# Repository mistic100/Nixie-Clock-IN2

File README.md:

# Nixie Clock IN-2

Check out my other projects:
- [Nixie Clock IN14](https://github.com/mistic100/Nixie-Clock-IN14)
- [Nixie Clock IN12](https://github.com/mistic100/Nixie-Clock-IN12)
- [IV-27 VFD Clock](https://github.com/mistic100/IV-27-Clock)

This is a Nixie Clock using small [IN-2 tubes](https://www.tube-tester.com/sites/nixie/data/I/IN-2/in-2.htm) and a 16x9 LED matrix. It was mostly inspired by this 3D model [80s Alarm Clock by Tom Seddon](https://sketchfab.com/3d-models/80s-alarm-clock-36aaecc458bc4e3ea907cdb9d538c9f1).

[More photos](https://photos.strangeplanet.fr/index.php?/category/268-horloge_nixie_in_2_mars_2026)

### Key features

- 3 buttons and 1 rotary encoder
- Zigbee connectivity
  - receive date-time
  - receive weather
  - send room temperature and humidity
  - can be toggled on/off
  - 3 generic buttons send click, double click, long click events
- small LED matrix with multiple screens
  - scrolling date
  - temperature
  - falling sand animation
  - Game of Life animation
  - fire animation
  - rain animation
- possibility to use a DS3231 RTC module (routed on the PCB but not available in current firmware)

### BOM

- ESP32-C6 SuperMini
- Adafruit Charlieplexed 16x9 LED matrix + IS31FL3731 driver
- 4x IN-2 Nixie tubes
- 2x INS-1 Nixie indicators
- Microchip HV5222 serial-to-parallel converter
- Adafruit 4 channels TTL level-shifter
- 4x APA106 5mm adressable LEDs
- BME280 ambient sensor
- EC11 rotary encoder
- 3x 6x6x4.3mm push buttons
- MPSA42 high voltage NPN transistor
- USB-C connector
- resistors, capacitors, diodes...

### Schematics

### PCB

### Case

## License

The Arduino code, the KiCad design and SolidWorks files are distributed under the Creative Commons 3.0 BY-SA license.

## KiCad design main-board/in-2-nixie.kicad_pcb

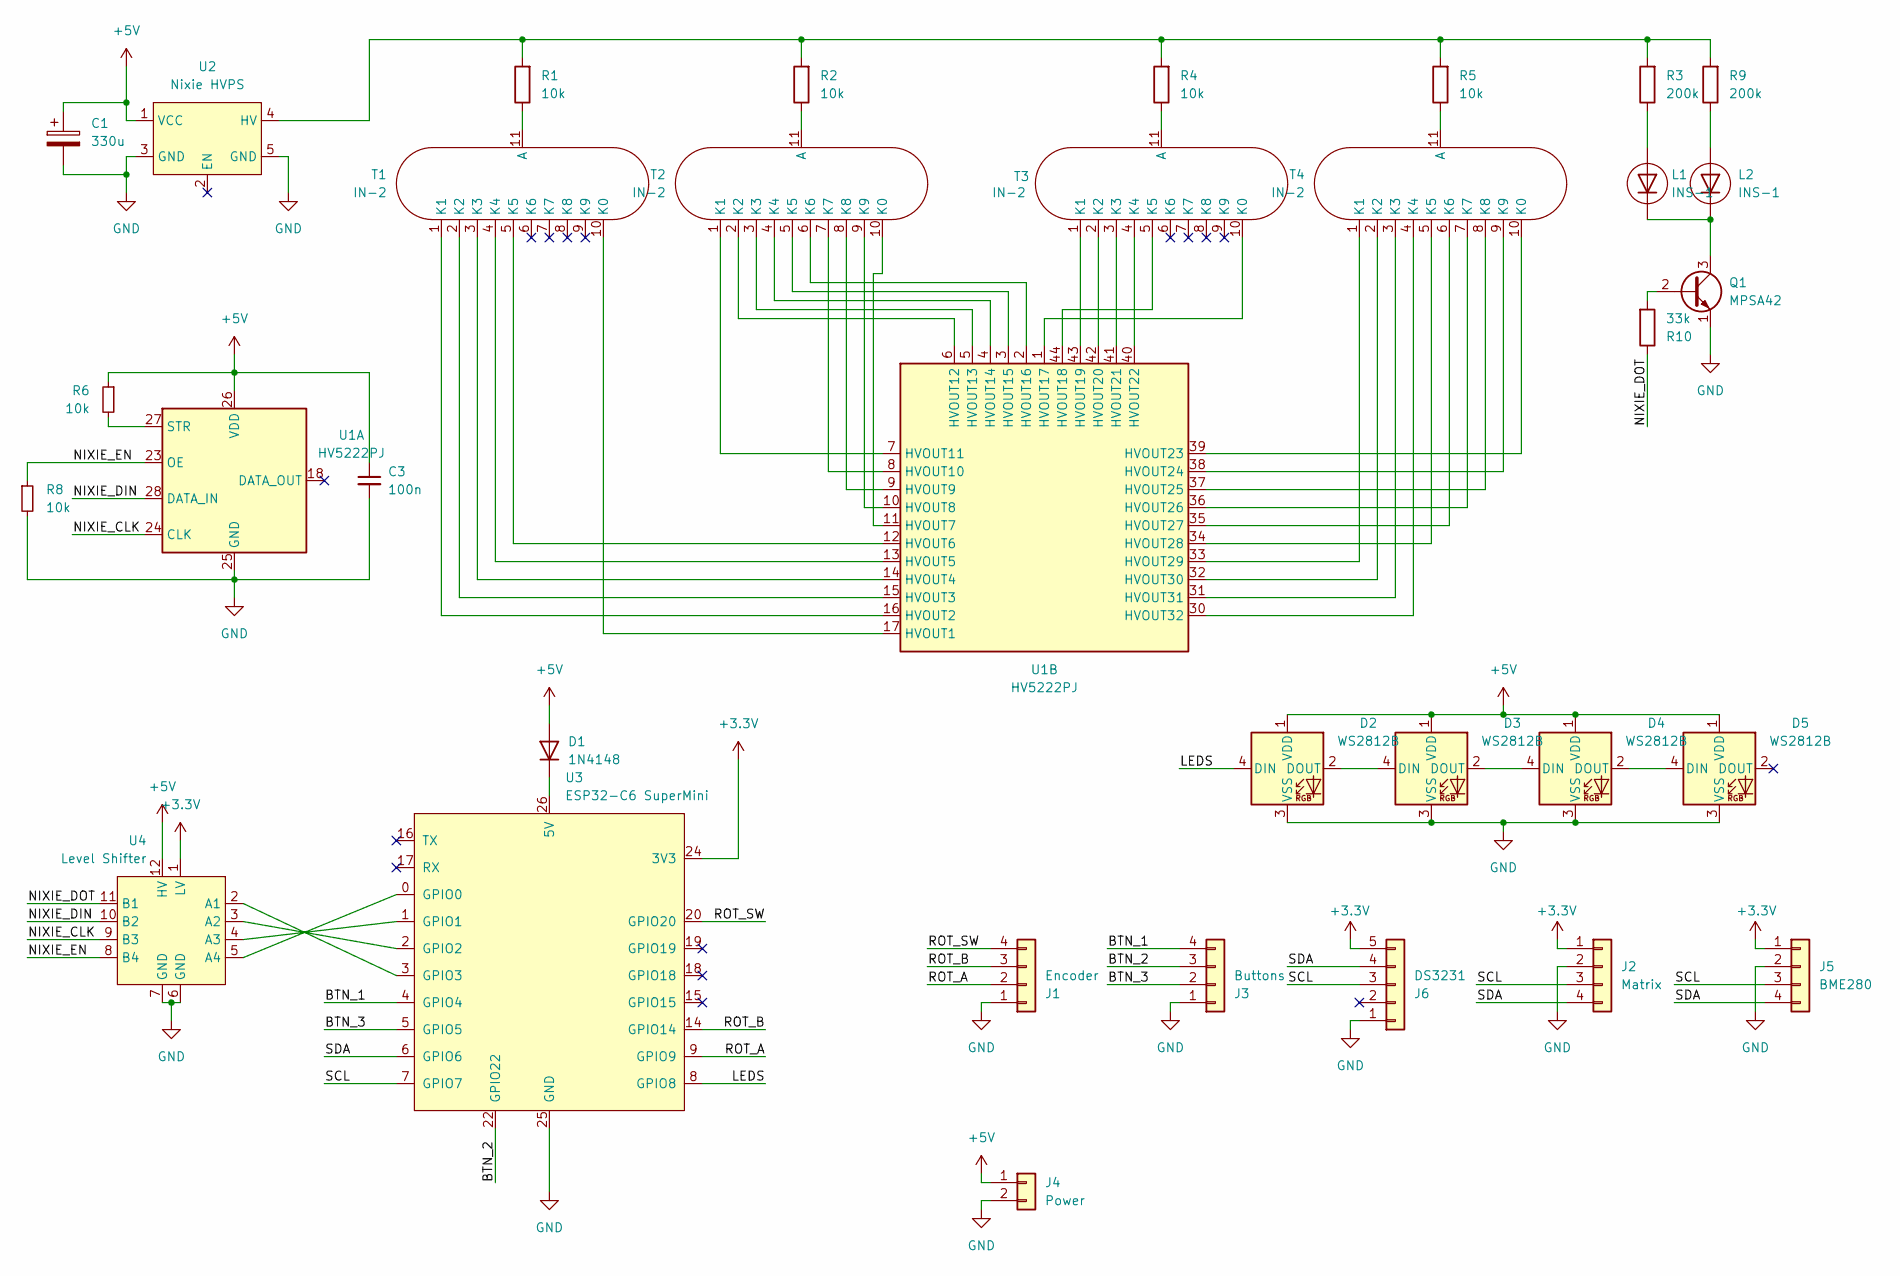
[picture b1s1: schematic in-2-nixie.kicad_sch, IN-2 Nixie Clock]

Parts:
C1: 330u; CP_Radial_D8.0mm_P3.50mm
C3: 100n; C_Disc_D5.0mm_W2.5mm_P5.00mm
D1: 1N4148; D_DO-35_SOD27_P7.62mm_Horizontal
D2, D3, D4, D5: WS2812B; APA106_D5-Staggered_Pins
J1: Encoder; PinHeader_1x04_P2.54mm_Vertical
J2: Matrix; PinHeader_1x04_P2.54mm_Vertical
J3: Buttons; PinHeader_1x04_P2.54mm_Vertical
J4: Power; JST_XH_B2B-XH-A_1x02_P2.50mm_Vertical
J5: BME280; PinHeader_1x04_P2.54mm_Vertical
J6: DS3231; PinHeader_1x05_P2.54mm_Vertical
L1, L2: INS-1; INS-1 Nixie Tube
Q1: MPSA42; TO-92_Inline
R1, R2, R4, R5: 10k; R_Axial_DIN0207_L6.3mm_D2.5mm_P7.62mm_Horizontal
R3, R9: 200k; R_Axial_DIN0207_L6.3mm_D2.5mm_P7.62mm_Horizontal
R6, R8: 10k; R_Axial_DIN0207_L6.3mm_D2.5mm_P2.54mm_Vertical
R10: 33k; R_Axial_DIN0207_L6.3mm_D2.5mm_P2.54mm_Vertical
T1, T2, T3, T4: IN-2; IN-2 Nixie Tube (w. pins)
U1: HV5222PJ; PLCC-44 LongPads
U2: Nixie HVPS; Neonwork Nixie Power Supply
U3: ESP32-C6 SuperMini
U4: Level Shifter; Adafruit Level Shifter

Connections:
+3.3V: J2.1, J5.1, J6.5, U3.24 (3V3), U4.1 (LV)
+5V: C1.1, C3.1, D1.2 (A), D2.1 (VDD), D3.1 (VDD), D4.1 (VDD), D5.1 (VDD), J4.1, R6.1, U1.26 (VDD), U2.1 (VCC), U4.12 (HV)
/BTN_1: J3.4, U3.4 (GPIO4)
/BTN_2: J3.3, U3.22 (GPIO22)
/BTN_3: J3.2, U3.5 (GPIO5)
/LEDS: D2.4 (DIN), U3.8 (GPIO8)
/NIXIE_CLK: U1.24 (CLK), U4.9 (B3)
/NIXIE_DIN: U1.28 (DATA_IN), U4.10 (B2)
/NIXIE_DOT: R10.1, U4.11 (B1)
/NIXIE_EN: R8.1, U1.23 (OE), U4.8 (B4)
/ROT_A: J1.2, U3.9 (GPIO9)
/ROT_B: J1.3, U3.14 (GPIO14)
/ROT_SW: J1.4, U3.20 (GPIO20)
/SCL: J2.3, J5.3, J6.3, U3.7 (GPIO7)
/SDA: J2.4, J5.4, J6.4, U3.6 (GPIO6)
GND: C1.2, C3.2, D2.3 (VSS), D3.3 (VSS), D4.3 (VSS), D5.3 (VSS), J1.1, J2.2, J3.1, J4.2, J5.2, J6.1, Q1.1 (E), R8.2, U1.25 (GND), U2.3 (GND), U2.5 (GND), U3.25 (GND), U4.6 (GND), U4.7 (GND)
unnamed: D1.1 (K), U3.26 (5V)
unnamed: D2.2 (DOUT), D3.4 (DIN)
unnamed: D3.2 (DOUT), D4.4 (DIN)
unnamed: D4.2 (DOUT), D5.4 (DIN)
unnamed: L1.2 (A), R3.1
unnamed: L1.1 (K), L2.1 (K), Q1.3 (C)
unnamed: L2.2 (A), R9.1
unnamed: Q1.2 (B), R10.2
unnamed: R1.1, T1.11 (A)
unnamed: T1.10 (K0), U1.17 (HVOUT1)
unnamed: T1.1 (K1), U1.16 (HVOUT2)
unnamed: T1.2 (K2), U1.15 (HVOUT3)
unnamed: T1.3 (K3), U1.14 (HVOUT4)
unnamed: T1.4 (K4), U1.13 (HVOUT5)
unnamed: T1.5 (K5), U1.12 (HVOUT6)
unnamed: R2.1, T2.11 (A)
unnamed: T2.10 (K0), U1.11 (HVOUT7)
unnamed: T2.1 (K1), U1.7 (HVOUT11)
unnamed: T2.2 (K2), U1.6 (HVOUT12)
unnamed: T2.3 (K3), U1.5 (HVOUT13)
unnamed: T2.4 (K4), U1.4 (HVOUT14)
unnamed: T2.5 (K5), U1.3 (HVOUT15)
unnamed: T2.6 (K6), U1.2 (HVOUT16)
unnamed: T2.7 (K7), U1.8 (HVOUT10)
unnamed: T2.8 (K8), U1.9 (HVOUT9)
unnamed: T2.9 (K9), U1.10 (HVOUT8)
unnamed: R4.1, T3.11 (A)
unnamed: T3.10 (K0), U1.1 (HVOUT17)
unnamed: T3.1 (K1), U1.43 (HVOUT19)
unnamed: T3.2 (K2), U1.42 (HVOUT20)
unnamed: T3.3 (K3), U1.41 (HVOUT21)
unnamed: T3.4 (K4), U1.40 (HVOUT22)
unnamed: T3.5 (K5), U1.44 (HVOUT18)
unnamed: R5.1, T4.11 (A)
unnamed: T4.10 (K0), U1.39 (HVOUT23)
unnamed: T4.1 (K1), U1.33 (HVOUT29)
unnamed: T4.2 (K2), U1.32 (HVOUT30)
unnamed: T4.3 (K3), U1.31 (HVOUT31)
unnamed: T4.4 (K4), U1.30 (HVOUT32)
unnamed: T4.5 (K5), U1.34 (HVOUT28)
unnamed: T4.6 (K6), U1.35 (HVOUT27)
unnamed: T4.7 (K7), U1.36 (HVOUT26)
unnamed: T4.8 (K8), U1.37 (HVOUT25)
unnamed: T4.9 (K9), U1.38 (HVOUT24)
unnamed: R6.2, U1.27 (STR)
unnamed: R1.2, R2.2, R3.2, R4.2, R5.2, R9.2, U2.4 (HV)
unnamed: U3.0 (GPIO0), U4.5 (A4)
unnamed: U3.1 (GPIO1), U4.4 (A3)
unnamed: U3.2 (GPIO2), U4.3 (A2)
unnamed: U3.3 (GPIO3), U4.2 (A1)

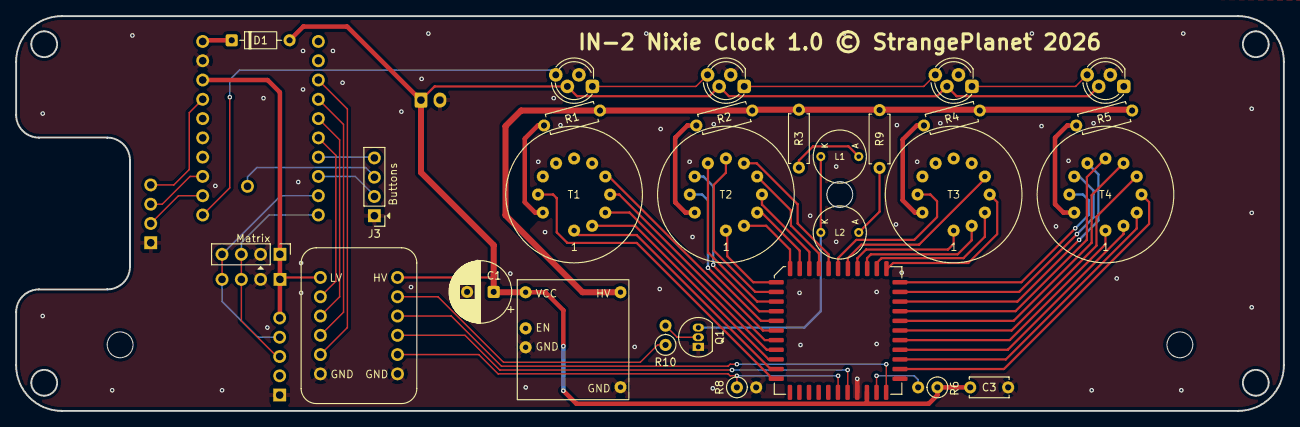
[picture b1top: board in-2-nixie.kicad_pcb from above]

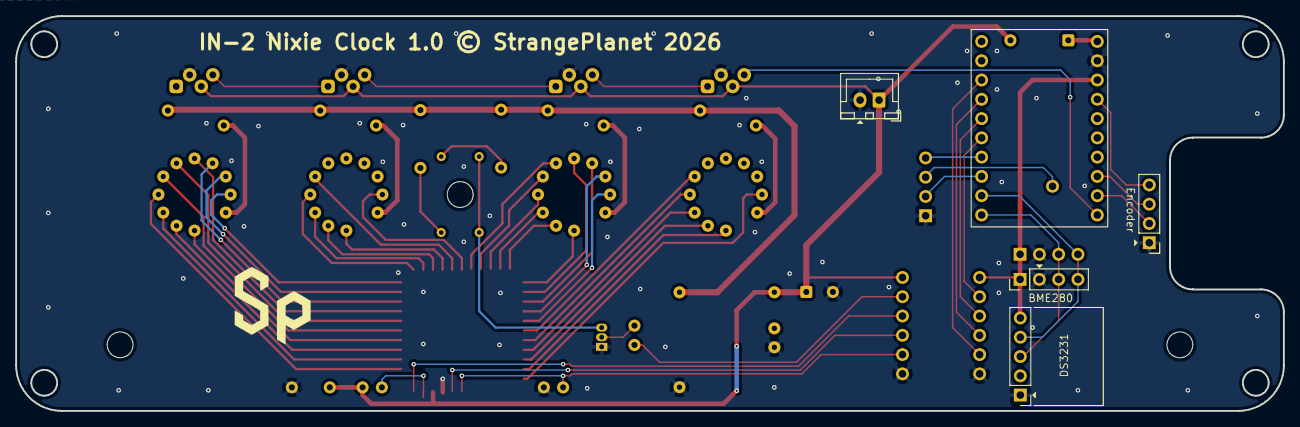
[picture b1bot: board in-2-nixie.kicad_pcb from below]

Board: 2 copper layers, 167.0 x 52.0 mm, 33 parts (5 on the bottom side), 66 nets.

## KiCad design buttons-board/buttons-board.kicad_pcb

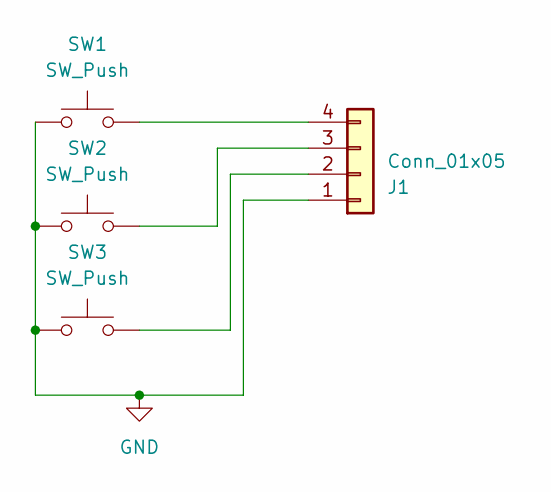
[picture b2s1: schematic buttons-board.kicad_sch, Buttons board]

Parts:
J1: Conn_01x05; PinHeader_1x04_P2.54mm_Horizontal
SW1, SW2, SW3: SW_Push; SW_PUSH_6mm_H4.3mm

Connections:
GND: J1.1, SW1.1, SW2.1, SW3.1
unnamed: J1.2, SW3.2
unnamed: J1.3, SW2.2
unnamed: J1.4, SW1.2

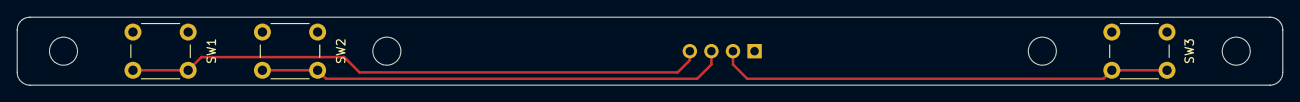
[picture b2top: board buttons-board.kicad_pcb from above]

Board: 2 copper layers, 149.0 x 8.0 mm, 4 parts (1 on the bottom side), 4 nets.

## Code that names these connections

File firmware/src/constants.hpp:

#pragma once

// zigbee configuration
#define ZIGBEE_MANUFACTURER "StrangePlanet"
#define ZIGBEE_MODEL "IN-2-Clock"
#define ZIGBEE_ENDPOINT_MAIN 1
#define ZIGBEE_ENDPOINT_BME280 2
#define ZIGBEE_ENDPOINT_LEDS 3
#define ZIGBEE_ENDPOINT_CUSTOM 10
#define ZIGBEE_CUSTOM_CLUSTER_ID 0xFF01
#define ZIGBEE_ATTR_ACTION_ID 0x0000
#define ZIGBEE_ATTR_WEATHER_ID 0x0001
#define ZIGBEE_ATTR_TEMP_OFFSET 0x0002

// screen matrix configuration
#define SCREEN_ROTATION 0
#define SCREEN_WIDTH 16
#define SCREEN_HEIGHT 9
#define SCREEN_BRIGHTNESS 20

// nixie driver configuration
#define DRIVER_DIN 2
#define DRIVER_CLK 1
#define DRIVER_OE 0

#define DOTS 3

#define ANTI_POISONING_INTERVAL_S 20 * 60
#define ANTI_POISONING_CYCLES 100

#define TEMP_DISPLAY_DURATION_S 30

// buttons configuration
#define ENCODER_A 9
#define ENCODER_B 14
#define ENCODER_SW 20

#define BTN_1 4
#define BTN_2 22
#define BTN_3 5

#define DOUBLE_CLICK_MS 300
#define LONG_CLICK_MS 500

// bme280 configuration
#define TEMP_UPDATE_INTERVAL_S 60

// leds configuration
#define LEDS_PIN RGB_BUILTIN
#define NUM_LEDS 6 // built-in + 4 + 1 for safety
#define LEDS_ORDER LED_COLOR_ORDER_RGB

// datetime configuration
#define TIMEZONE "CET-1CEST,M3.5.0,M10.5.0/3" // https://github.com/esp8266/Arduino/blob/master/cores/esp8266/TZ.h
#define LOCALIZED_DATE

#ifdef LOCALIZED_DATE
const char* DAY_NAMES[7] = {
    "DIM",
    "LUN",
    "MAR",
    "MER",
    "JEU",
    "VEN",
    "SAM"
};

const char* MONTH_NAMES[12] = {
    "JAN",
    "FEV",
    "MAR",
    "AVR",
    "MAI",
    "JUN",
    "JUI",
    "AOU",
    "SEP",
    "OCT",
    "NOV",
    "DEC"
};
#endif

// nixie driver configuration
const uint8_t PIN_H10[6] = {
    1,
    2,
    3,
    4,
    5,
    6};

const uint8_t PIN_H[10] = {
    7,
    11,
    12,
    13,
    14,
    15,
    16,
    10,
    9,
    8};

const uint8_t PIN_M10[6] = {
    17,
    19,
    20,
    21,
    22,
    18};

const uint8_t PIN_M[10] = {
    23,
    29,
    30,
    31,
    32,
    28,
    27,
    26,
    25,
    24};

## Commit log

2026-01-28 working
2026-01-29 ground plane
2026-02-10 firmware
2026-02-21 update model
2026-02-22 pcb final
2026-02-22 Cleanup code
2026-03-21 update firmware
2026-03-21 fix encoder routing
2026-03-23 fix nixie driver
2026-03-26 Fix time init, ZB led control, ZB temp offset
2026-03-27 cleanup
2026-03-27 last fix
2026-03-28 Fix sceen state
2026-03-29 Save state and mode
2026-03-29 Temporary time display while off
2026-03-29 Remove OTA partition
2026-03-29 Add renders
2026-06-27 Improve stability
2026-06-27 Remove useless time offset
    Zigbee library now returns Unix time instead of ZB time
